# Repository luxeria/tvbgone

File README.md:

tvbgone
=======

Kleines Projekt um Kicad und die MSP430 besser kennen zu lernen.

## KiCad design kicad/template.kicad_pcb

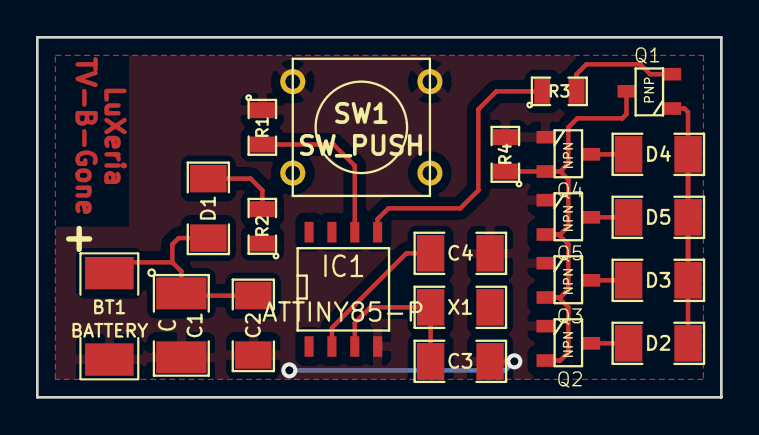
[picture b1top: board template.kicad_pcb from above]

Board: 2 copper layers, 38.0 x 20.0 mm, 22 parts (0 on the bottom side), 15 nets.

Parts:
BT1: BATTERY; SM2010
C1: C; SM1210L
C2, C3, C4: C; SM1206
D1, D2, D3, D4, D5: LED; SM1206
IC1: ATTINY85-P; SO8N
Q1: PNP; SOT23
Q2, Q3, Q4, Q5: NPN; SOT23
R1, R2, R3, R4: R; SM0805
SW1: SW_PUSH; SW_PUSH_SMALL
X1: QUARTZCMS4; SM1206

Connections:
GND: BT1.2, C1.2, C2.2, C3.2, C4.2, IC1.4, Q2.1, Q3.1, Q4.1, Q5.1, R1.1, R4.2, SW1.1
unnamed: Q1.2, R3.2
unnamed: D4.2, Q4.3
unnamed: D5.2, Q5.3
unnamed: D3.2, Q3.3
unnamed: D2.2, Q2.3
unnamed: Q1.3, Q2.2, Q3.2, Q4.2, Q5.2, R4.1
unnamed: C3.1, IC1.3, X1.1
unnamed: IC1.1, SW1.2
unnamed: IC1.6, R1.2
unnamed: IC1.5, R3.1
unnamed: IC1.7, R2.1
unnamed: D1.2, R2.2
unnamed: C4.1, IC1.2
VCC: BT1.1, C1.1, C2.1, D1.1, D2.1, D3.1, D4.1, D5.1, IC1.8, Q1.1

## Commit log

2013-02-14 readme angepasst
2013-02-14 .gitignore
2013-02-14 leeres Schema
2013-02-14 Projekt zu leerem Schema
2013-02-15 schematic-sheet geändert auf A3, Title=TV-B-Gone, Company=LuXeria
2013-02-15 schematic-sheet auf Revision=Dev geändert
2013-02-15 footprint erstellt für msp4302g*
2013-02-15 schematic-symbol erstellt für msp430g2*
2013-02-15 zwischengespeicherte libs zu .gitignore hinzugefügt
2013-02-15 .gitignore auskommentiert, damit alle alles nachvollziehen können
2013-02-15 ge-cache-te datei entfernt aus repo
2013-02-15 kommentare im .gitignore geändert
2013-02-15 mcu in schema eingefügt
2013-02-15 Dokumentation begonnen
2013-02-15 .gitignore aktualisiert
2013-02-16 in 'doc' etwas zu Code-Konventionen geschrieben und Kopf- und Fusszeilen korrigiert
2013-02-16 weitere exceptions zum .gitignore hinzugefügt
2013-02-16 Dokumentation vorbereitet
2013-02-16 Einleitung
2013-02-16 Header eingefügt
2013-02-16 Kleine Änderungen
2013-02-16 Einleitung zu RC5 begonnen
2013-02-16 tvbgone.tex wieder zum projekt hinzugefügt (merge-conflict)
2013-02-16 fehler im tvbgone.tex korrigiert
2013-02-16 *.swp entfernt
2013-02-16 Bild zur Modulation von RC-5
2013-02-16 Modulation
2013-02-16 Anforderungen
2013-02-16 einige Anforderungen
2013-02-16 Anforderungen ergänzt
2013-02-19 MSP430 Toolchain dokumentiert für Linux
2013-02-19 erstes programm kompiliert und geflasht
2013-02-19 hello.c an code-konventionen angepasst
2013-02-20 Struktur der Dokumentation umgestellt
2013-02-20 Tippfehler korrigiert
2013-02-20 Einleitung erweitert
2013-02-27 Toolchain unter Windows begonnen
2013-02-27 Toolchain Windows: Download
2013-02-28 Toolchain Windows: Installation Treiber
2013-02-28 Toolchain Windows: Installation Treiber ergänzt
2013-02-28 Links in der Fussnote
2013-03-01 Installation Treiber unter Windows
2013-03-02 Installation mspgcc und mspdebug unter windows fertig
2013-03-03 DCO Konfiguration 16MHz
2013-03-06 einfaches Hello World in doc begonnen.
2013-03-07 Einrückung korrigiert
2013-03-07 Hello World kommentiert
2013-03-30 Toolchain Installation für Arch dokumnetiert
2013-03-30 einige Korrekturen in der Rechtschreibung vorgenommen
2013-04-02 Hardware Konventionen begonnen
2013-04-02 Tabelle begonnen.
2013-04-02 Tabelle erweitert
2013-04-02 DIN 40719-2 und DIN EN 81346-2 ergänzt
2013-04-02 Vorschlag angepasst
2013-04-02 pdf aktualisiert
2013-04-02 kleine Ergänzungn
2013-04-02 Kopf der Tabelle angepasst
2013-04-03 kleine Ergänzungen
2013-04-03 Allgemeine Richtlinien für Schaltpläne begonnen
2013-04-03 Allgemeine Richtlinien für PCBs begonnen
2013-04-03 Allgemeine Richtlinien für PCBs ergänzt
2013-04-03 Allgemeine Richtlinien für Schaltpläne besser umschrieben
2013-04-03 Allgemeine Richtlinien für Schaltpläne erweitert
2013-04-06 Beispielprogramm zu GPIO/Pushbutton/Interrupt erstellt
2013-04-06 Darstellung verbessert in Beispielcode
2013-04-06 Timer-Beispiel hinzugefügt
2013-04-07 SMCLK on P1.4
2013-04-07 pdf merged
